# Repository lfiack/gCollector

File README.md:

# gCollector
Garbage collector robot for FreeRTOS Labs

## How to get the project
This project uses submodules, use the following command to get everything :
```
git clone --recursive git@github.com:lfiack/gCollector.git
```

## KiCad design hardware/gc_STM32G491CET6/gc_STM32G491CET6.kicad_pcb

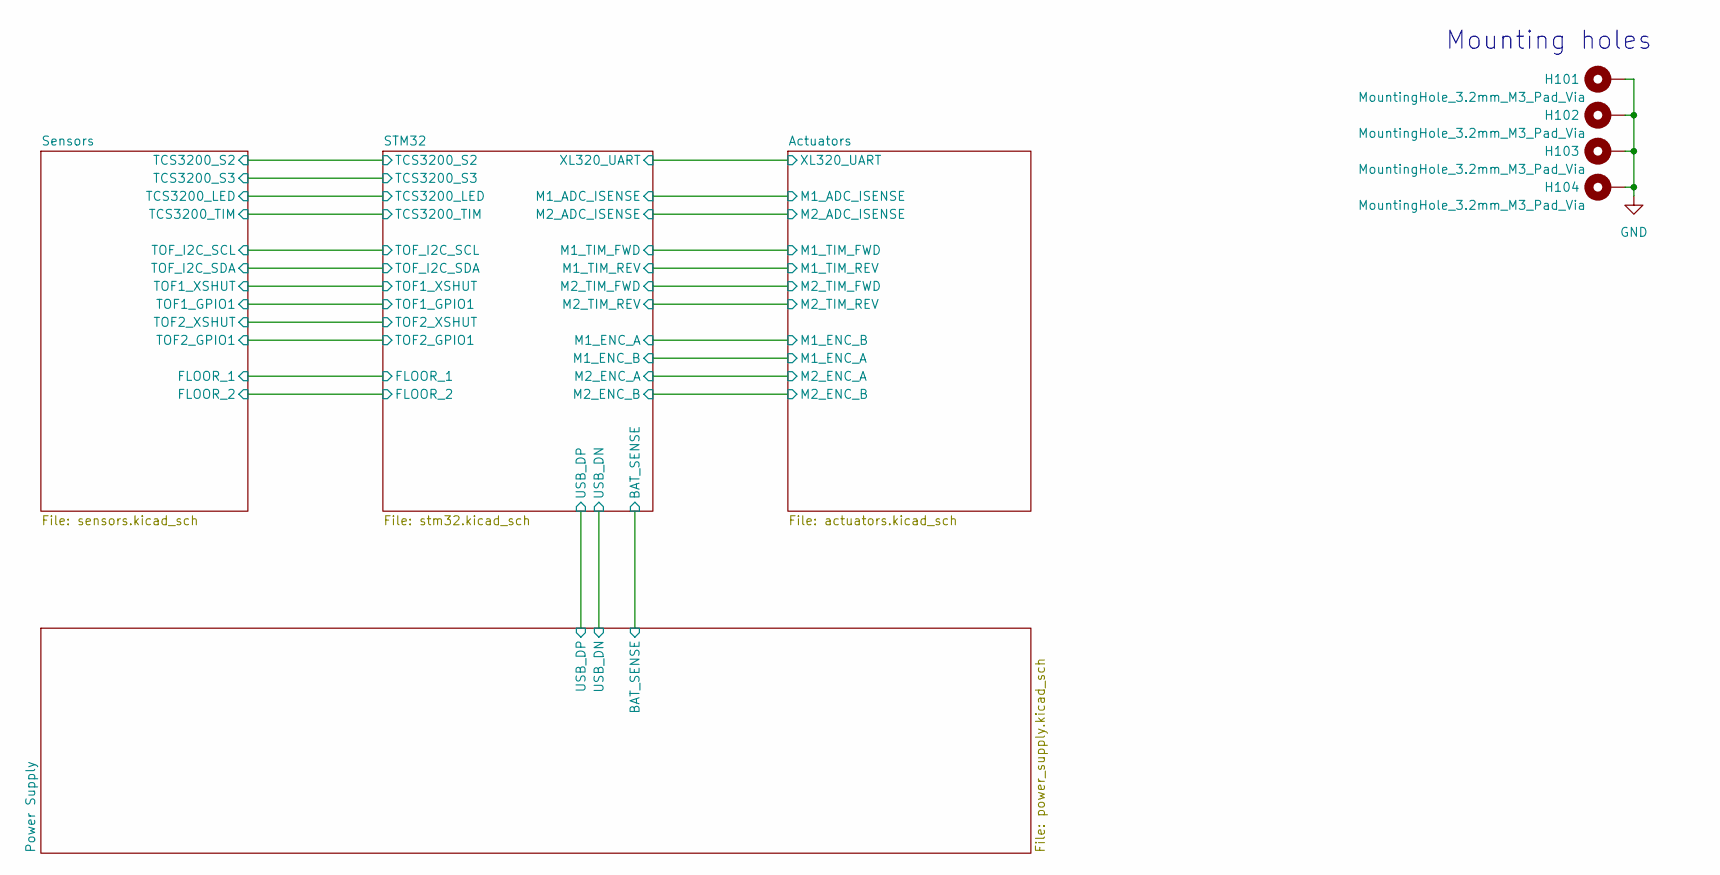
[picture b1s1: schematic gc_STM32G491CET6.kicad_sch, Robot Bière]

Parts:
H101, H102, H103, H104: MountingHole_3.2mm_M3_Pad_Via

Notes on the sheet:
Mounting holes

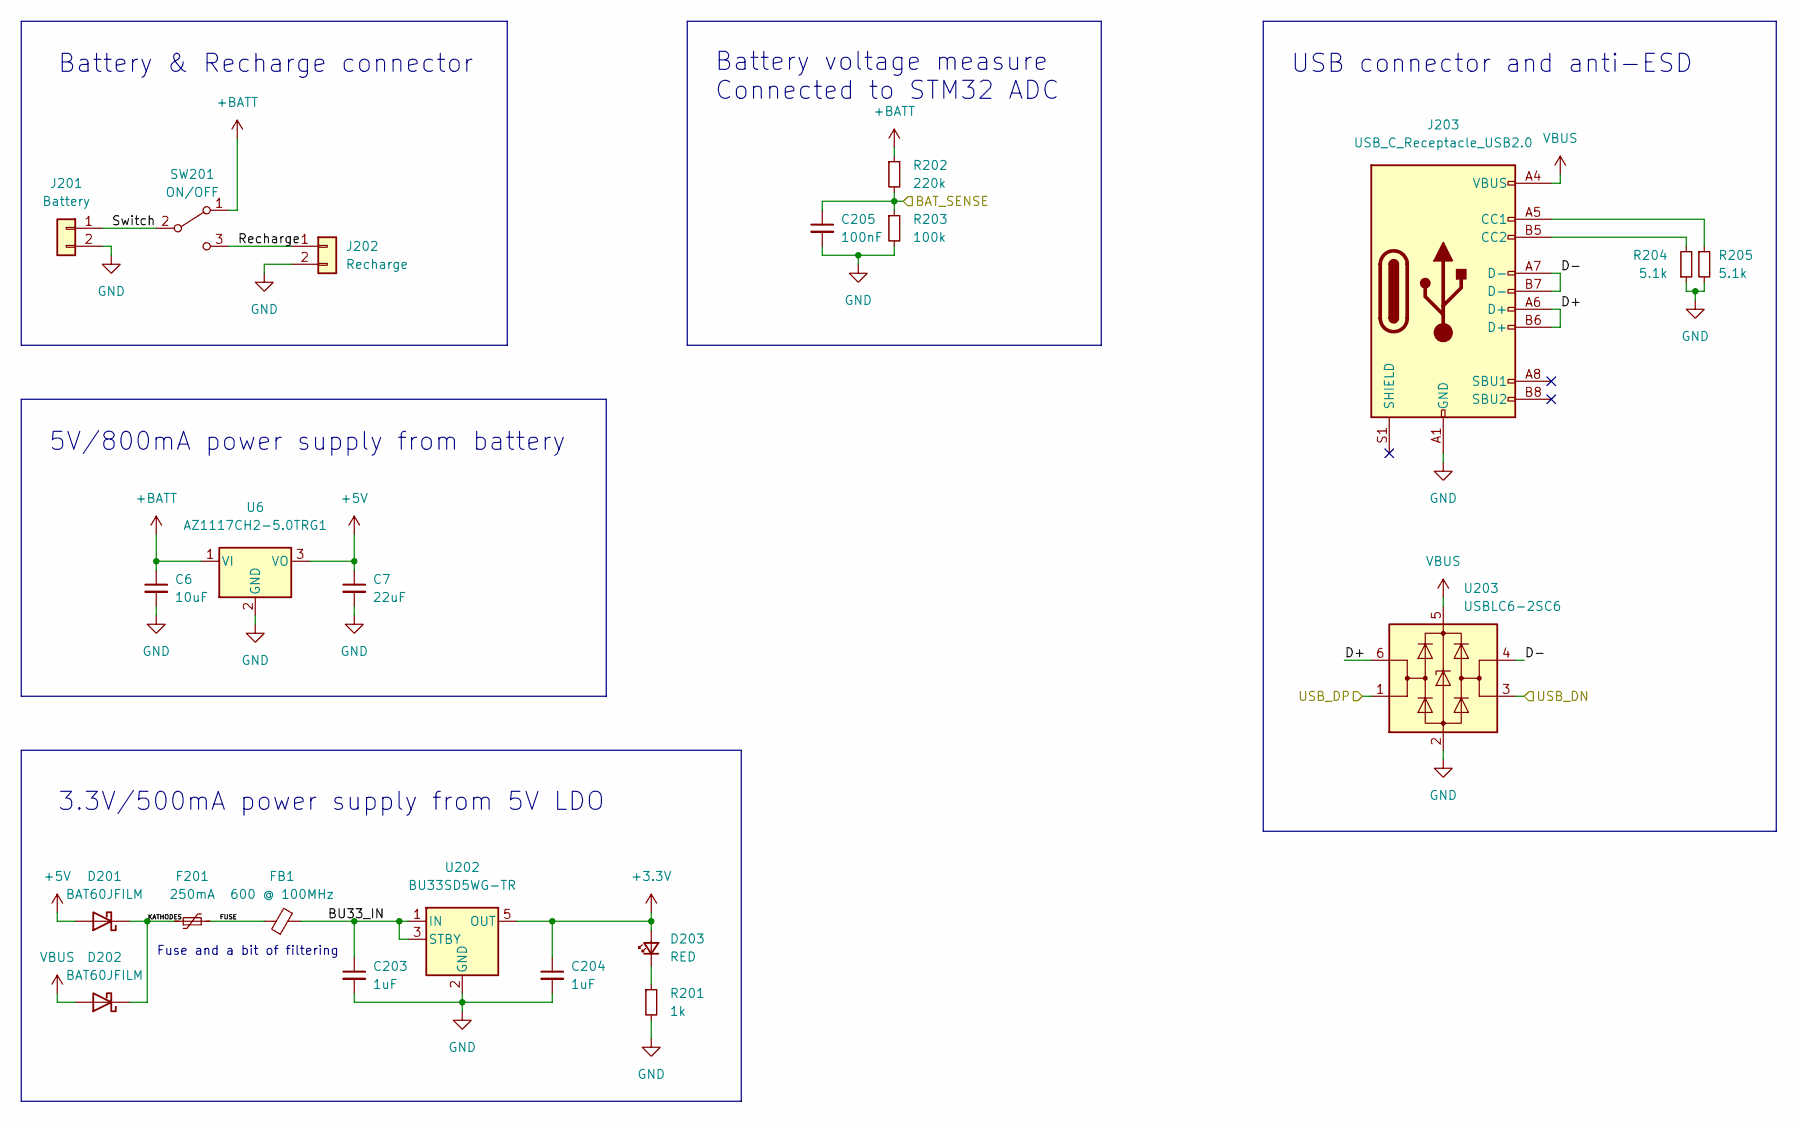
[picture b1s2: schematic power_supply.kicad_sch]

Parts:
C6: 10uF; C_0603_1608Metric_Pad1.08x0.95mm_HandSolder; Farnell 2113070
C7: 22uF; C_0603_1608Metric_Pad1.08x0.95mm_HandSolder; Farnell 2426957
C203, C204: 1uF; C_0603_1608Metric
C205: 100nF; C_0603_1608Metric
D201, D202: BAT60JFILM; D_SOD-323
D203: RED; LED_0603_1608Metric
F201: 250mA; Fuse_1206_3216Metric_Pad1.42x1.75mm_HandSolder; Farnell 2834880
FB1: 600 @ 100MHz; L_0805_2012Metric_Pad1.15x1.40mm_HandSolder; Farnell 2292460
J201: Battery; JST_XH_B2B-XH-A_1x02_P2.50mm_Vertical
J202: Recharge; JST_XH_B2B-XH-A_1x02_P2.50mm_Vertical
J203: USB_C_Receptacle_USB2.0; USB_C_Receptacle_HRO_TYPE-C-31-M-12
R201: 1k; R_0603_1608Metric
R202: 220k; R_0603_1608Metric
R203: 100k; R_0603_1608Metric
R204, R205: 5.1k; R_0603_1608Metric
SW201: ON/OFF; RS_Switch_448-0747
U6: AZ1117CH2-5.0TRG1; SOT-223-3_TabPin2; Farnell 3942512
U202: BU33SD5WG-TR; SOT-23-5
U203: USBLC6-2SC6; SOT-23-6

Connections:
+3.3V: C204.1, D203.2 (A), U202.5 (OUT); also elsewhere on the board
+5V: C7.1, D201.2 (A), U6.3 (VO)
/Power Supply/BAT_SENSE: C205.1, R202.2, R203.1; also elsewhere on the board
/Power Supply/BU33_IN: C203.1, FB1.2, U202.1 (IN), U202.3 (STBY)
/Power Supply/D+: J203.A6 (D+), J203.B6 (D+), U203.6 (I/O1)
/Power Supply/D-: J203.A7 (D-), J203.B7 (D-), U203.4 (I/O2)
/Power Supply/FUSE: F201.2, FB1.1
/Power Supply/KATHODES: D201.1 (K), D202.1 (K), F201.1
/Power Supply/Recharge: J202.1, SW201.3 (C)
/Power Supply/Switch: J201.1, SW201.2 (B)
/Power Supply/USB_DN: U203.3 (I/O2); also elsewhere on the board
/Power Supply/USB_DP: U203.1 (I/O1); also elsewhere on the board
unnamed: D203.1 (K), R201.1
unnamed: J203.A5 (CC1), R205.1
unnamed: J203.B5 (CC2), R204.2
VBUS: D202.2 (A), J203.A4 (VBUS), J203.A9 (VBUS), J203.B4 (VBUS), J203.B9 (VBUS), U203.5 (VBUS)

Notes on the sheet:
Fuse and a bit of filtering
3.3V/500mA power supply from 5V LDO
Battery & Recharge connector
5V/800mA power supply from battery
Battery voltage measure Connected to STM32 ADC
USB connector and anti-ESD

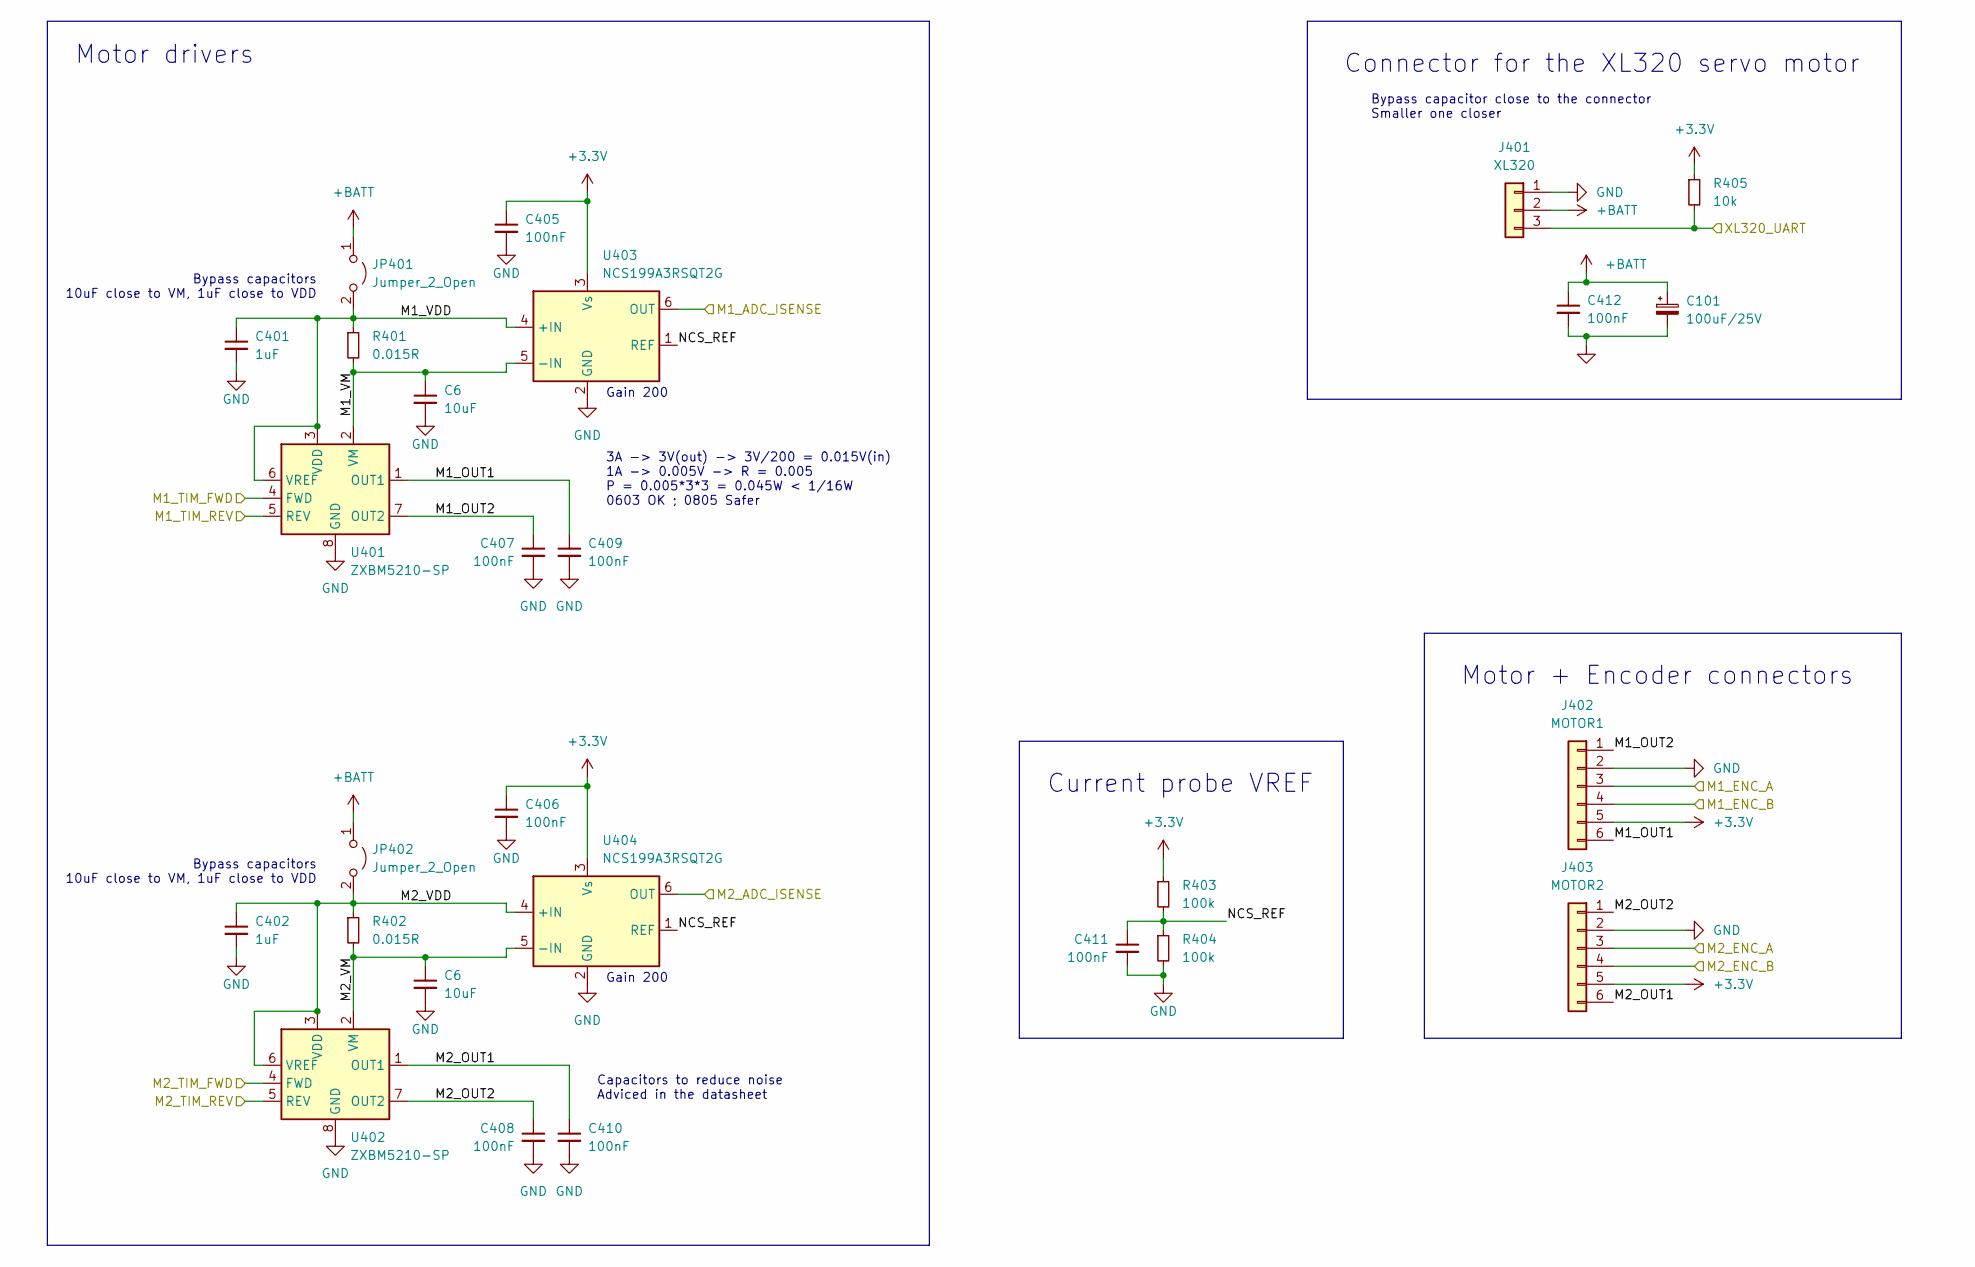
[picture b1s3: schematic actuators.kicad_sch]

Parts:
C6: 10uF; C_0603_1608Metric_Pad1.08x0.95mm_HandSolder; Farnell 2113070
C101: 100uF/25V; CP_Elec_6.3x7.7
C401, C402: 1uF; C_0603_1608Metric
C405, C406, C407, C408, C409, C410, C411, C412: 100nF; C_0603_1608Metric
J401: XL320; JST_XH_B3B-XH-A_1x03_P2.50mm_Vertical
J402: MOTOR1; JST_XH_B6B-XH-A_1x06_P2.50mm_Vertical
J403: MOTOR2; JST_XH_B6B-XH-A_1x06_P2.50mm_Vertical
JP401, JP402: Jumper_2_Open; PinHeader_1x02_P2.54mm_Vertical
R401, R402: 0.015R; R_0805_2012Metric
R403, R404: 100k; R_0603_1608Metric
R405: 10k; R_0603_1608Metric
U401, U402: ZXBM5210-SP; Diodes_SO-8EP
U403, U404: NCS199A3RSQT2G; SOT-363_SC-70-6; Farnell 2981170

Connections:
+3.3V: C405.1, C406.1, J402.5, J403.5, R403.1, R405.1, U403.3 (Vs), U404.3 (Vs); also elsewhere on the board
/Actuators/M1_ADC_ISENSE: U403.6 (OUT); also elsewhere on the board
/Actuators/M1_ENC_A: J402.3; also elsewhere on the board
/Actuators/M1_ENC_B: J402.4; also elsewhere on the board
/Actuators/M1_OUT1: C409.1, J402.6, U401.1 (OUT1)
/Actuators/M1_OUT2: C407.1, J402.1, U401.7 (OUT2)
/Actuators/M1_TIM_FWD: U401.4 (FWD); also elsewhere on the board
/Actuators/M1_TIM_REV: U401.5 (REV); also elsewhere on the board
/Actuators/M1_VDD: C401.1, JP401.2 (B), R401.1, U401.3 (VDD), U401.6 (VREF), U403.4 (+IN)
/Actuators/M2_ADC_ISENSE: U404.6 (OUT); also elsewhere on the board
/Actuators/M2_ENC_A: J403.3; also elsewhere on the board
/Actuators/M2_ENC_B: J403.4; also elsewhere on the board
/Actuators/M2_OUT1: C410.1, J403.6, U402.1 (OUT1)
/Actuators/M2_OUT2: C408.1, J403.1, U402.7 (OUT2)
/Actuators/M2_TIM_FWD: U402.4 (FWD); also elsewhere on the board
/Actuators/M2_TIM_REV: U402.5 (REV); also elsewhere on the board
/Actuators/M2_VDD: C402.1, JP402.2 (B), R402.1, U402.3 (VDD), U402.6 (VREF), U404.4 (+IN)
/Actuators/NCS_REF: C411.1, R403.2, R404.1, U403.1 (REF), U404.1 (REF)
/Actuators/XL320_UART: J401.3, R405.2; also elsewhere on the board

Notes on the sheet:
Bypass capacitor close to the connector Smaller one closer
Current probe VREF
Motor drivers
Gain 200
Bypass capacitors 10uF close to VM, 1uF close to VDD
Connector for the XL320 servo motor
Capacitors to reduce noise Adviced in the datasheet
Motor + Encoder connectors
3A -> 3V(out) -> 3V/200 = 0.015V(in) 1A -> 0.005V -> R = 0.005 P = 0.005*3*3 = 0.045W < 1/16W 0603 OK ; 0805 Safer

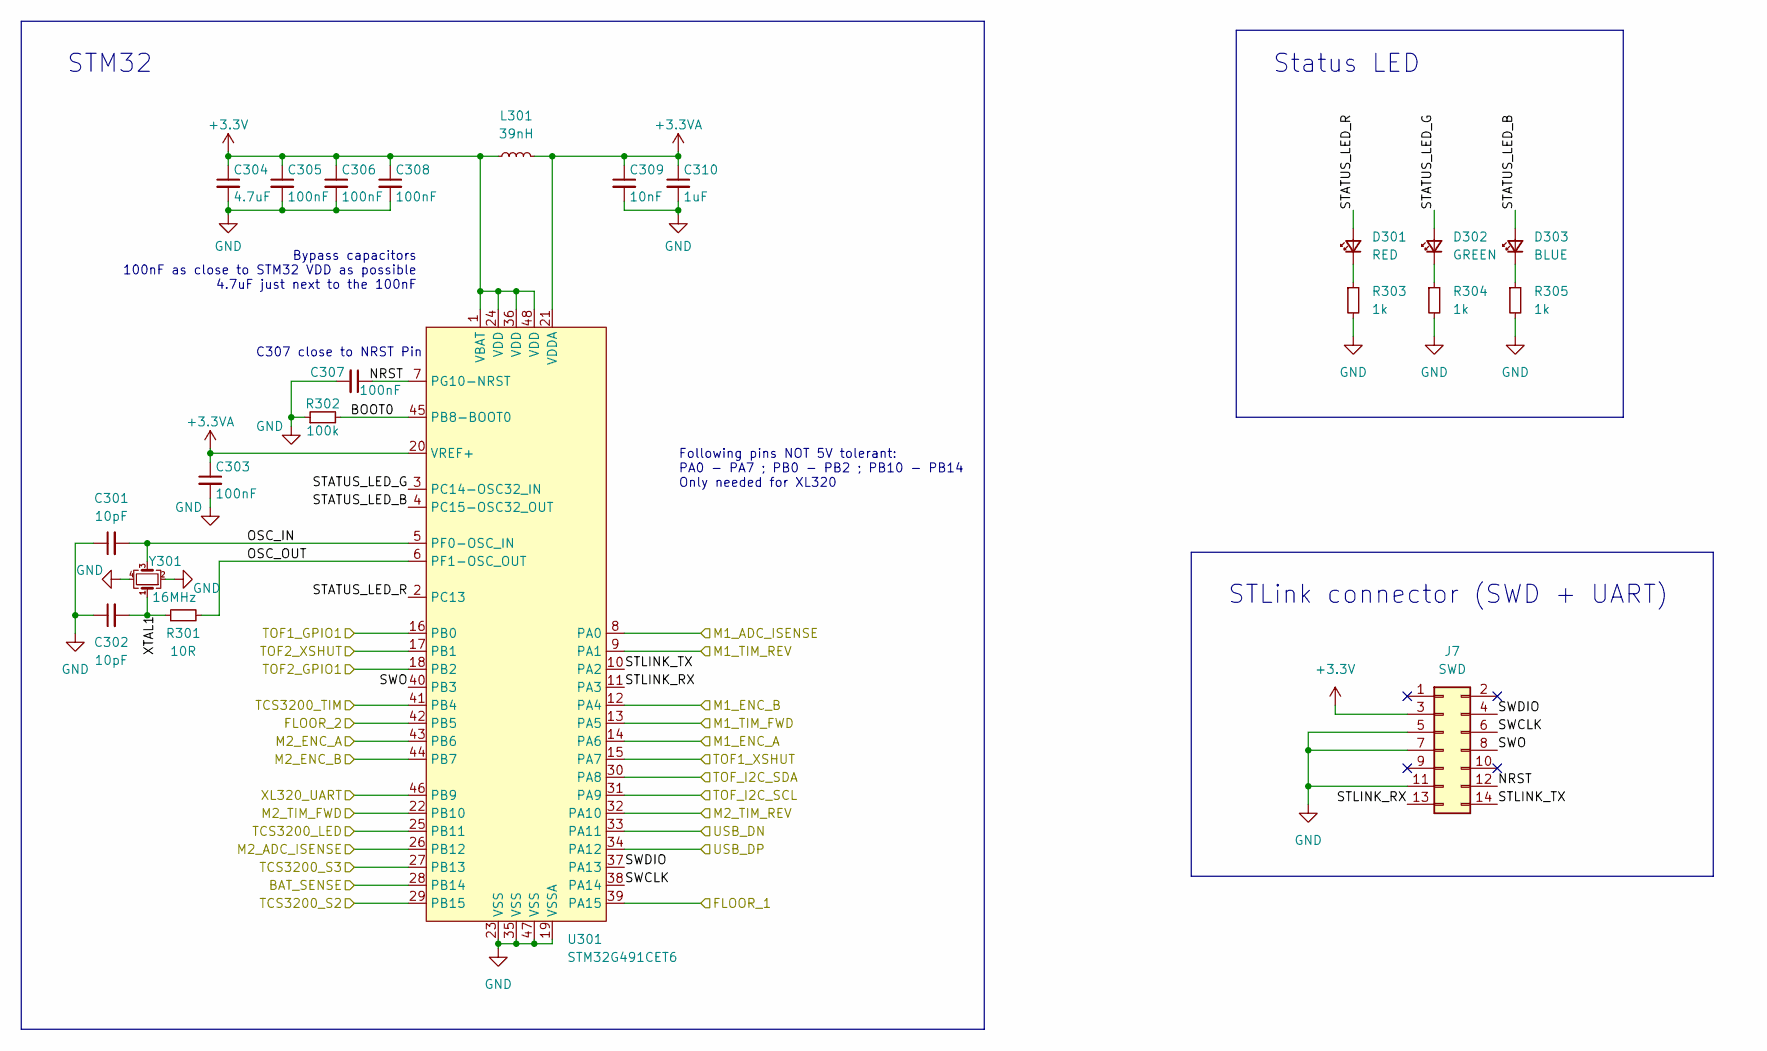
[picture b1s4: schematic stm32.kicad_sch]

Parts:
C301, C302: 10pF; C_0603_1608Metric
C303: 100nF; C_0603_1608Metric; Farnell 3013398
C304: 4.7uF; C_0603_1608Metric; Farnell 3013398
C305, C306, C307, C308: 100nF; C_0603_1608Metric
C309: 10nF; C_0603_1608Metric
C310: 1uF; C_0603_1608Metric; Farnell 3013398
D301: RED; LED_0603_1608Metric
D302: GREEN; LED_0603_1608Metric
D303: BLUE; LED_0603_1608Metric
J7: Conn_02x07_Odd_Even; PinHeader_2x07_P1.27mm_Vertical_SMD; Farnell 3226055
L301: 39nH; L_0603_1608Metric
R301: 10R; R_0603_1608Metric
R302: 100k; R_0603_1608Metric
R303, R304, R305: 1k; R_0603_1608Metric
U301: STM32G491CET6; LQFP-48_7x7mm_P0.5mm
Y301: 16MHz; Crystal_SMD_EuroQuartz_MT-4Pin_3.2x2.5mm; Farnell 2853935

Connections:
+3.3V: C304.1, C305.1, C306.1, C308.1, J7.3, L301.1, U301.1 (VBAT), U301.24 (VDD), U301.36 (VDD), U301.48 (VDD); also elsewhere on the board
+3.3VA: C303.1, C309.1, C310.1, L301.2, U301.20 (VREF+), U301.21 (VDDA)
/Actuators/M1_ADC_ISENSE: U301.8 (PA0); also elsewhere on the board
/Actuators/M1_ENC_A: U301.12 (PA4); also elsewhere on the board
/Actuators/M1_ENC_B: U301.14 (PA6); also elsewhere on the board
/Actuators/M1_TIM_FWD: U301.13 (PA5); also elsewhere on the board
/Actuators/M1_TIM_REV: U301.9 (PA1); also elsewhere on the board
/Actuators/M2_ADC_ISENSE: U301.26 (PB12); also elsewhere on the board
/Actuators/M2_ENC_A: U301.43 (PB6); also elsewhere on the board
/Actuators/M2_ENC_B: U301.44 (PB7); also elsewhere on the board
/Actuators/M2_TIM_FWD: U301.22 (PB10); also elsewhere on the board
/Actuators/M2_TIM_REV: U301.32 (PA10); also elsewhere on the board
/Actuators/XL320_UART: U301.46 (PB9); also elsewhere on the board
/Power Supply/BAT_SENSE: U301.28 (PB14); also elsewhere on the board
/Power Supply/USB_DN: U301.33 (PA11); also elsewhere on the board
/Power Supply/USB_DP: U301.34 (PA12); also elsewhere on the board
/STM32/BOOT0: R302.2, U301.45 (PB8-BOOT0)
/STM32/FLOOR_1: U301.39 (PA15); also elsewhere on the board
/STM32/FLOOR_2: U301.42 (PB5); also elsewhere on the board
/STM32/NRST: C307.1, J7.12, U301.7 (PG10-NRST)
/STM32/OSC_IN: C301.2, U301.5 (PF0-OSC_IN), Y301.3
/STM32/OSC_OUT: R301.2, U301.6 (PF1-OSC_OUT)
/STM32/STATUS_LED_B: D303.2 (A), U301.4 (PC15-OSC32_OUT)
/STM32/STATUS_LED_G: D302.2 (A), U301.3 (PC14-OSC32_IN)
/STM32/STATUS_LED_R: D301.2 (A), U301.2 (PC13)
/STM32/STLINK_RX: J7.13, U301.11 (PA3)
/STM32/STLINK_TX: J7.14, U301.10 (PA2)
/STM32/SWCLK: J7.6, U301.38 (PA14)
/STM32/SWDIO: J7.4, U301.37 (PA13)
/STM32/SWO: J7.8, U301.40 (PB3)
/STM32/TCS3200_LED: U301.25 (PB11); also elsewhere on the board
/STM32/TCS3200_S2: U301.29 (PB15); also elsewhere on the board
/STM32/TCS3200_S3: U301.27 (PB13); also elsewhere on the board
/STM32/TCS3200_TIM: U301.41 (PB4); also elsewhere on the board
/STM32/TOF1_GPIO1: U301.16 (PB0); also elsewhere on the board
/STM32/TOF1_XSHUT: U301.15 (PA7); also elsewhere on the board
/STM32/TOF2_GPIO1: U301.18 (PB2); also elsewhere on the board
/STM32/TOF2_XSHUT: U301.17 (PB1); also elsewhere on the board
/STM32/TOF_I2C_SCL: U301.31 (PA9); also elsewhere on the board
/STM32/TOF_I2C_SDA: U301.30 (PA8); also elsewhere on the board
/STM32/XTAL1: C302.2, R301.1, Y301.1
unnamed: D301.1 (K), R303.1
unnamed: D302.1 (K), R304.1
unnamed: D303.1 (K), R305.1

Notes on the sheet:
STM32
Bypass capacitors 100nF as close to STM32 VDD as possible 4.7uF just next to the 100nF
Following pins NOT 5V tolerant: PA0 - PA7 ; PB0 - PB2 ; PB10 - PB14 Only needed for XL320
Status LED
STLink connector (SWD + UART)
C307 close to NRST Pin

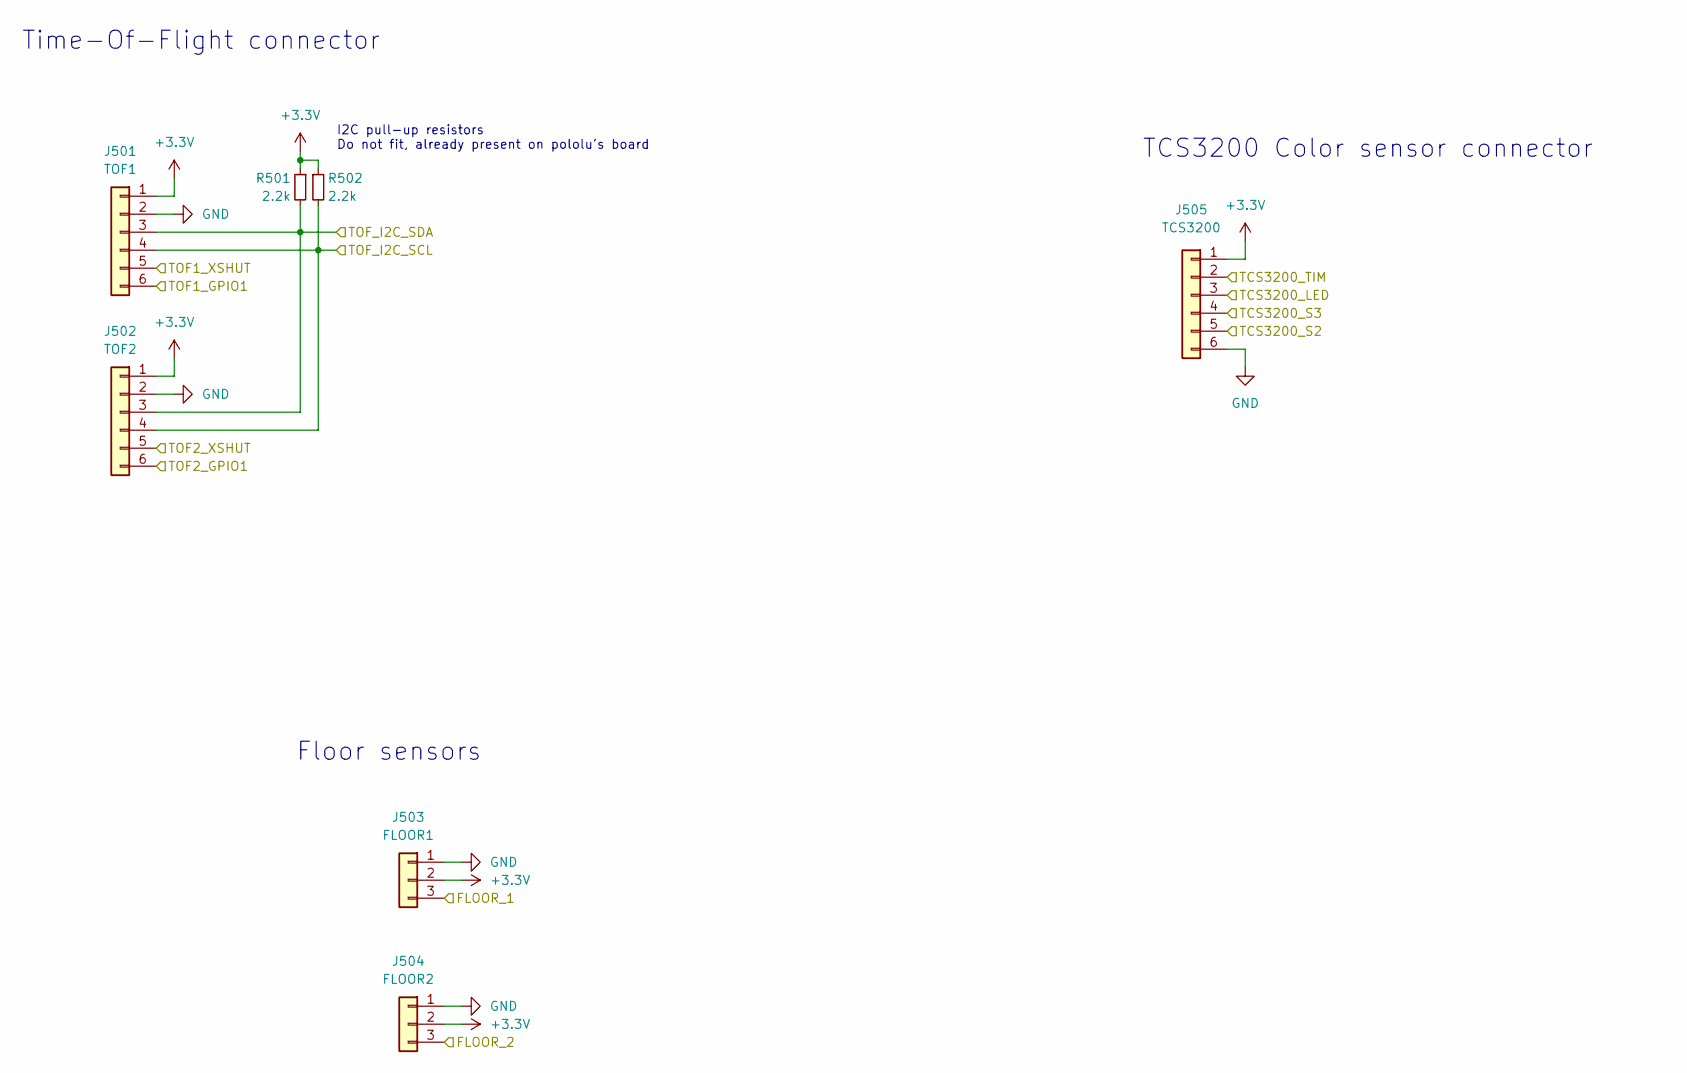
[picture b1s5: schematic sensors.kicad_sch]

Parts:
J501: TOF1; JST_XH_B6B-XH-A_1x06_P2.50mm_Vertical
J502: TOF2; JST_XH_B6B-XH-A_1x06_P2.50mm_Vertical
J503: FLOOR1; JST_XH_B3B-XH-A_1x03_P2.50mm_Vertical
J504: FLOOR2; JST_XH_B3B-XH-A_1x03_P2.50mm_Vertical
J505: TCS3200; JST_XH_B6B-XH-A_1x06_P2.50mm_Vertical
R501, R502: 2.2k; R_0603_1608Metric

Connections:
+3.3V: J501.1, J502.1, J503.2, J504.2, J505.1, R501.1, R502.1; also elsewhere on the board
/STM32/FLOOR_1: J503.3; also elsewhere on the board
/STM32/FLOOR_2: J504.3; also elsewhere on the board
/STM32/TCS3200_LED: J505.3; also elsewhere on the board
/STM32/TCS3200_S2: J505.5; also elsewhere on the board
/STM32/TCS3200_S3: J505.4; also elsewhere on the board
/STM32/TCS3200_TIM: J505.2; also elsewhere on the board
/STM32/TOF1_GPIO1: J501.6; also elsewhere on the board
/STM32/TOF1_XSHUT: J501.5; also elsewhere on the board
/STM32/TOF2_GPIO1: J502.6; also elsewhere on the board
/STM32/TOF2_XSHUT: J502.5; also elsewhere on the board
/STM32/TOF_I2C_SCL: J501.4, J502.4, R502.2; also elsewhere on the board
/STM32/TOF_I2C_SDA: J501.3, J502.3, R501.2; also elsewhere on the board

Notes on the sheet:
TCS3200 Color sensor connector
Time-Of-Flight connector
Floor sensors
I2C pull-up resistors Do not fit, already present on pololu's board

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
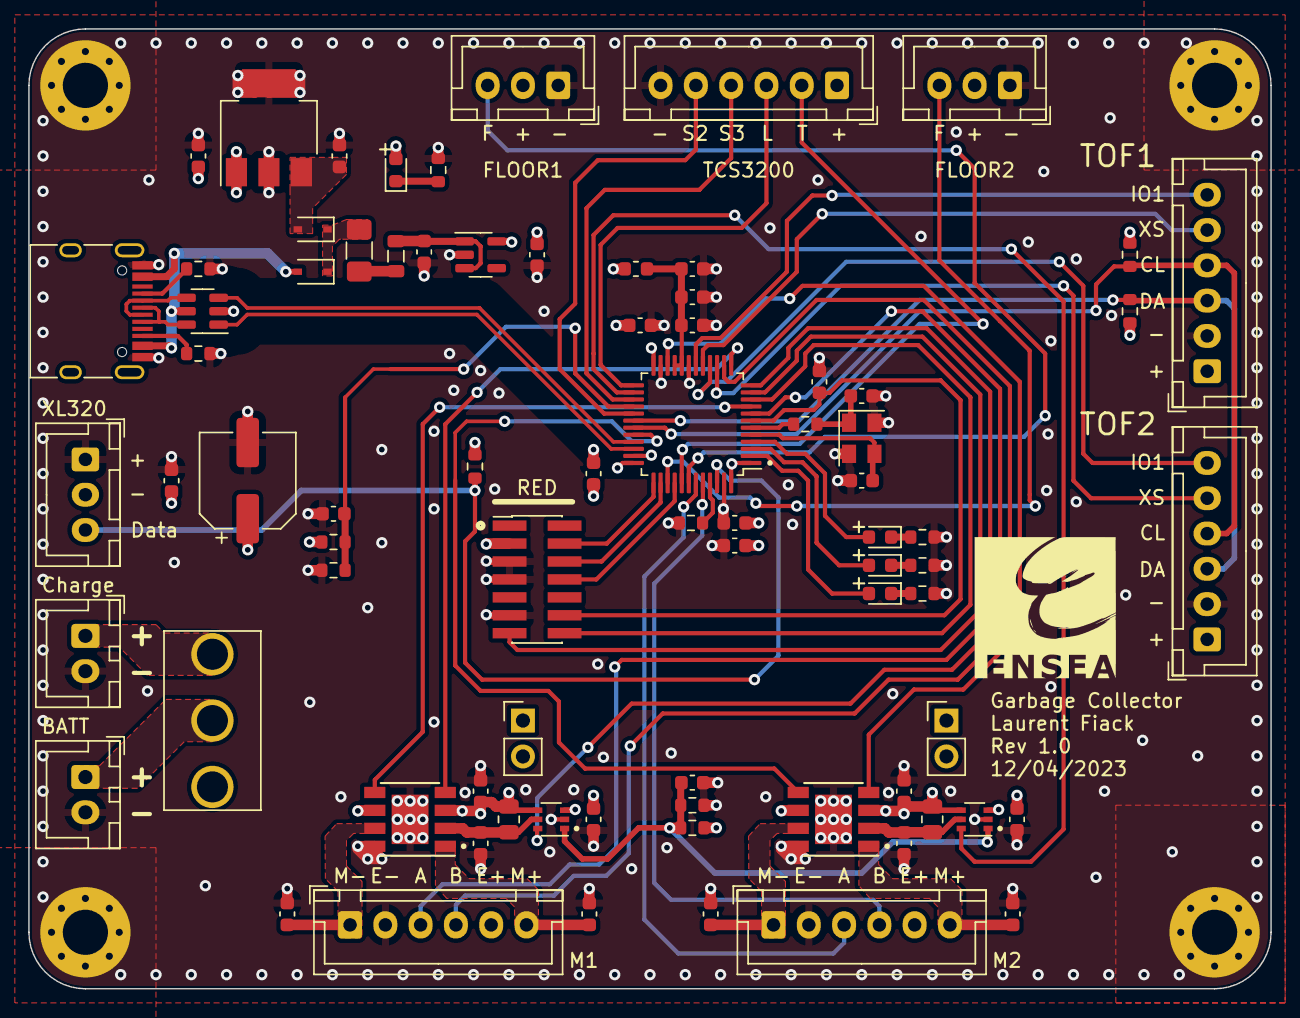
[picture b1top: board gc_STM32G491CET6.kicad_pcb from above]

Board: 4 copper layers, 88.0 x 68.0 mm, 82 parts (0 on the bottom side), 67 nets.

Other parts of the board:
C6#2, C6#3: 10uF; C_0603_1608Metric
C413: 100uF/25V; CP_Elec_6.3x7.7

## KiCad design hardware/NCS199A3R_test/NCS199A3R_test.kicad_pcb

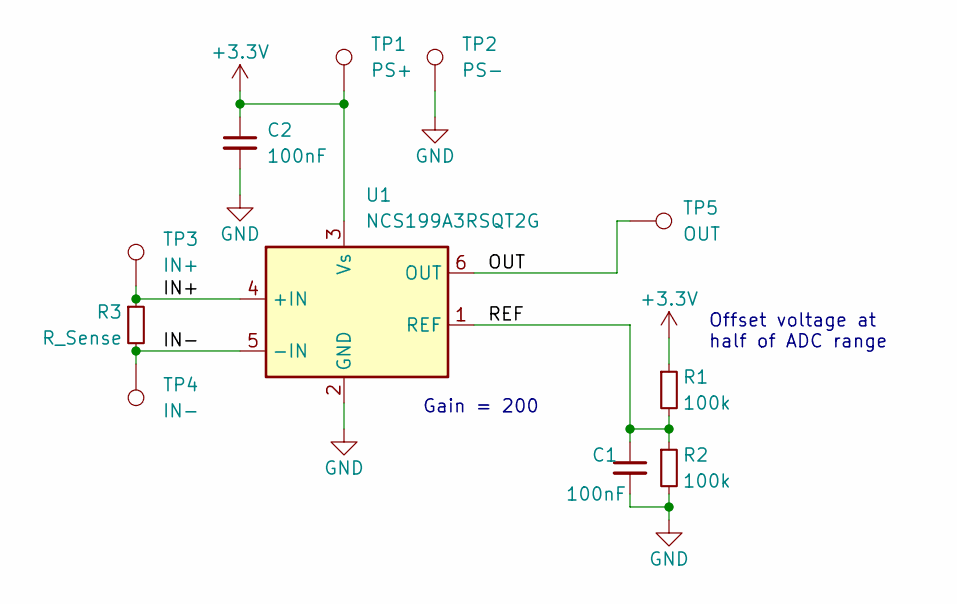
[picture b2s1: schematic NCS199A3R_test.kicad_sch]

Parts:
C1, C2: 100nF; C_0603_1608Metric_Pad1.08x0.95mm_HandSolder
R1, R2: 100k; R_0603_1608Metric_Pad0.98x0.95mm_HandSolder
R3: R_Sense; R_0805_2012Metric_Pad1.20x1.40mm_HandSolder
TP1: PS+; PinHeader_1x01_P2.54mm_Vertical
TP2: PS-; PinHeader_1x01_P2.54mm_Vertical
TP3: IN+; PinHeader_1x01_P2.54mm_Vertical
TP4: IN-; PinHeader_1x01_P2.54mm_Vertical
TP5: OUT; PinHeader_1x01_P2.54mm_Vertical
U1: NCS199A3RSQT2G; SOT-363_SC-70-6_Handsoldering

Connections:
+3.3V: C2.1, R1.1, TP1.1, U1.3 (Vs)
/IN+: R3.1, TP3.1, U1.4 (+IN)
/IN-: R3.2, TP4.1, U1.5 (-IN)
/OUT: TP5.1, U1.6 (OUT)
/REF: C1.1, R1.2, R2.1, U1.1 (REF)
GND: C1.2, C2.2, R2.2, TP2.1, U1.2 (GND)

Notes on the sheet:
Gain = 200
Offset voltage at half of ADC range

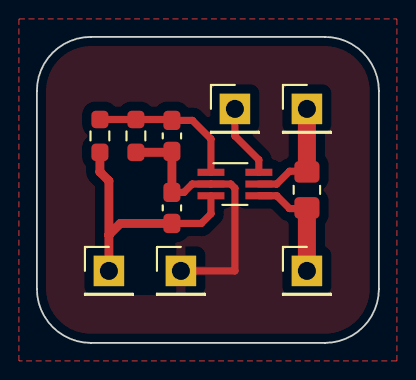
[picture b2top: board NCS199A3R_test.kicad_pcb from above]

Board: 2 copper layers, 19.0 x 17.0 mm, 11 parts (0 on the bottom side), 6 nets.

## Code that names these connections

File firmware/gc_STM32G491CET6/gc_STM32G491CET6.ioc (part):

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Mcu.Name=STM32G491C(C-E)Tx
Mcu.Package=LQFP48
Mcu.UserName=STM32G491CETx
PA0.GPIOParameters=GPIO_Label
PA0.GPIO_Label=M1_ADC_ISENSE
PA0.Mode=IN1-Single-Ended
PA0.Signal=ADC1_IN1
PA1.GPIOParameters=GPIO_Label
PA1.GPIO_Label=M1_TIM_REV
PA1.Signal=S_TIM2_CH2
PA10.GPIOParameters=GPIO_Label
PA10.GPIO_Label=M2_TIM_REV
PA10.Signal=S_TIM2_CH4
PA11.Mode=Device
PA11.Signal=USB_DM
PA12.Mode=Device
PA12.Signal=USB_DP
PA13.Mode=Trace_Asynchronous_SW
PA13.Signal=SYS_JTMS-SWDIO
PA14.Mode=Trace_Asynchronous_SW
PA14.Signal=SYS_JTCK-SWCLK
PA15.GPIOParameters=GPIO_Label
PA15.GPIO_Label=FLOOR_1
PA15.Signal=GPXTI15
PA2.GPIOParameters=GPIO_Label
PA2.GPIO_Label=STLINK_TX
PA2.Mode=Asynchronous
PA2.Signal=USART2_TX
PA3.GPIOParameters=GPIO_Label
PA3.GPIO_Label=STLINK_RX
PA3.Mode=Asynchronous
PA3.Signal=USART2_RX
PA4.GPIOParameters=GPIO_Label
PA4.GPIO_Label=M1_ENC_B
PA4.Signal=S_TIM3_CH2
PA5.GPIOParameters=GPIO_Label
PA5.GPIO_Label=M1_TIM_FWD
PA5.Signal=S_TIM2_CH1
PA6.GPIOParameters=GPIO_Label
PA6.GPIO_Label=M1_ENC_A
PA6.Signal=S_TIM3_CH1
PA7.GPIOParameters=GPIO_Label
PA7.GPIO_Label=TOF1_XSHUT
PA7.Signal=GPIO_Output
PA8.GPIOParameters=GPIO_Label
PA8.GPIO_Label=TOF_I2C_SDA
PA8.Mode=I2C
PA8.Signal=I2C2_SDA
PA9.GPIOParameters=GPIO_Label
PA9.GPIO_Label=TOF_I2C_SCL
PA9.Mode=I2C
PA9.Signal=I2C2_SCL
PB0.GPIOParameters=GPIO_Label
PB0.GPIO_Label=TOF1_GPIO1
PB0.Signal=GPXTI0
PB1.GPIOParameters=GPIO_Label
PB1.GPIO_Label=TOF2_XSHUT
PB1.Signal=GPIO_Output
PB10.GPIOParameters=GPIO_Label
PB10.GPIO_Label=M2_TIM_FWD
PB10.Signal=S_TIM2_CH3
PB11.GPIOParameters=GPIO_Label
PB11.GPIO_Label=TCS3200_LED
PB11.Signal=GPIO_Output
PB12.GPIOParameters=GPIO_Label
PB12.GPIO_Label=M2_ADC_ISENSE
PB12.Mode=IN11-Single-Ended
PB12.Signal=ADC1_IN11
PB13.GPIOParameters=GPIO_Label
PB13.GPIO_Label=TCS3200_S3
PB13.Signal=GPIO_Output
PB14.GPIOParameters=GPIO_Label
PB14.GPIO_Label=BAT_SENSE
PB14.Mode=IN5-Single-Ended
PB14.Signal=ADC1_IN5
PB15.GPIOParameters=GPIO_Label
PB15.GPIO_Label=TCS3200_S2
PB15.Signal=GPIO_Output
PB2.GPIOParameters=GPIO_Label
PB2.GPIO_Label=TOF2_GPIO1
PB2.Signal=GPXTI2
PB3.Mode=Trace_Asynchronous_SW
PB3.Signal=SYS_JTDO-SWO
PB4.GPIOParameters=GPIO_Label
PB4.GPIO_Label=TCS3200_TIM
PB4.Signal=S_TIM16_CH1
PB5.GPIOParameters=GPIO_Label
PB5.GPIO_Label=FLOOR_2
PB5.Signal=GPXTI5
PB6.GPIOParameters=GPIO_Label
PB6.GPIO_Label=M2_ENC_A
PB6.Signal=S_TIM4_CH1
PB7.GPIOParameters=GPIO_Label
PB7.GPIO_Label=M2_ENC_B
PB7.Signal=S_TIM4_CH2
PB9.GPIOParameters=GPIO_Label
PB9.GPIO_Label=XL320_UART
PB9.Mode=Half_duplex(single_wire_mode)
PB9.Signal=USART3_TX
PC13.GPIOParameters=GPIO_Label
PC13.GPIO_Label=LED_R
PC13.Signal=GPIO_Output
PC14-OSC32_IN.GPIOParameters=GPIO_Label
PC14-OSC32_IN.GPIO_Label=LED_G
PC14-OSC32_IN.Signal=GPIO_Output
PC15-OSC32_OUT.GPIOParameters=GPIO_Label
PC15-OSC32_OUT.GPIO_Label=LED_B
PC15-OSC32_OUT.Signal=GPIO_Output
PF0-OSC_IN.Mode=HSE-External-Oscillator
PF0-OSC_IN.Signal=RCC_OSC_IN
PF1-OSC_OUT.Mode=HSE-External-Oscillator
PF1-OSC_OUT.Signal=RCC_OSC_OUT
RCC.HSE_VALUE=16000000
RCC.SYSCLKFreq_VALUE=170000000
RCC.SYSCLKSource=RCC_SYSCLKSOURCE_PLLCLK
board=custom

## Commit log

2022-12-06 Current probe test board
2022-12-07 panelization
2022-12-21 STM32 sheet
2022-12-21 test
2022-12-21 corrected submodule (I guess?)
2022-12-23 Schematics + rough placement
2023-04-04 placement
2023-04-07 started routing
2023-04-11 routing V1
2023-04-12 silkscreen
2023-04-13 routing
2023-04-14 tined border
2023-05-26 added test project for cubeIDE
2023-05-29 updated witns kicad lib
2023-05-29 shell submodule
2023-05-29 shell
2023-05-30 update witns kicad lib
